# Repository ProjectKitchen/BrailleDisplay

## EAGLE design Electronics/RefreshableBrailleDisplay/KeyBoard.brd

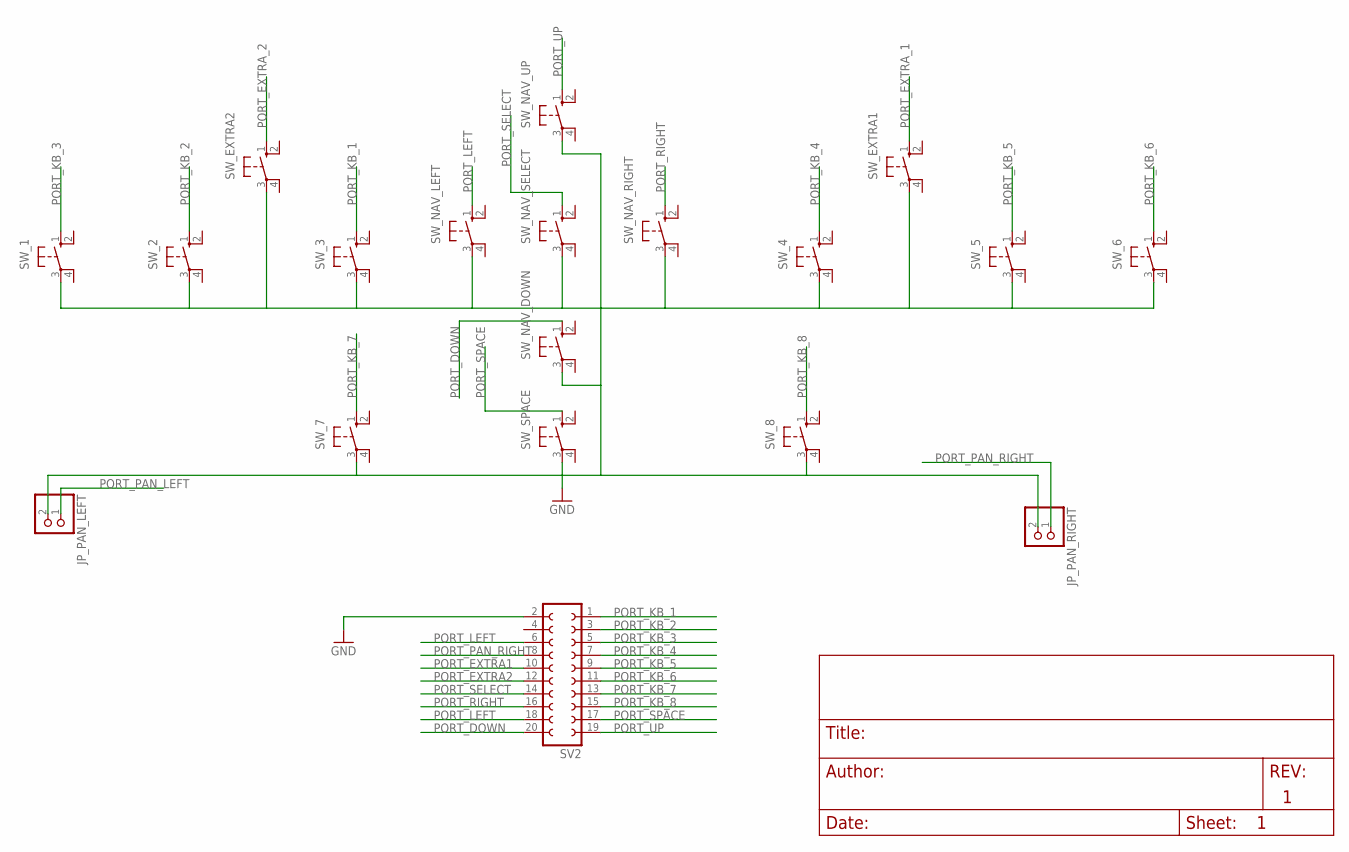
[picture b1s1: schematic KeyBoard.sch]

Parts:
JP_PAN_LEFT: PINHD-1X2; 1X02
JP_PAN_RIGHT: PINHD-1X2; 1X02
SV2: FE10-2
SW_1, SW_2, SW_3, SW_4, SW_5, SW_6, SW_7, SW_8: 10-XX; B3F-10XX
SW_EXTRA1, SW_EXTRA2: 10-XX; B3F-10XX
SW_NAV_DOWN: 10-XX; B3F-10XX
SW_NAV_LEFT: 10-XX; B3F-10XX
SW_NAV_RIGHT: 10-XX; B3F-10XX
SW_NAV_SELECT: 10-XX; B3F-10XX
SW_NAV_UP: 10-XX; B3F-10XX
SW_SPACE: 10-XX; B3F-10XX

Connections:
GND: JP_PAN_LEFT.2, JP_PAN_RIGHT.2, SV2.2, SW_1.3, SW_2.3, SW_3.3, SW_4.3, SW_5.3, SW_6.3, SW_7.3, SW_8.3, SW_EXTRA1.3, SW_EXTRA2.3, SW_NAV_DOWN.3, SW_NAV_LEFT.3, SW_NAV_RIGHT.3, SW_NAV_SELECT.3, SW_NAV_UP.3, SW_SPACE.3
PORT_DOWN: SV2.20, SW_NAV_DOWN.1 (S)
PORT_EXTRA1: SV2.10
PORT_EXTRA2: SV2.12
PORT_EXTRA_1: SW_EXTRA1.1 (S)
PORT_EXTRA_2: SW_EXTRA2.1 (S)
PORT_KB_1: SV2.1, SW_3.1 (S)
PORT_KB_2: SV2.3, SW_2.1 (S)
PORT_KB_3: SV2.5, SW_1.1 (S)
PORT_KB_4: SV2.7, SW_4.1 (S)
PORT_KB_5: SV2.9, SW_5.1 (S)
PORT_KB_6: SV2.11, SW_6.1 (S)
PORT_KB_7: SV2.13, SW_7.1 (S)
PORT_KB_8: SV2.15, SW_8.1 (S)
PORT_LEFT: SV2.6, SV2.18, SW_NAV_LEFT.1 (S)
PORT_PAN_LEFT: JP_PAN_LEFT.1
PORT_PAN_RIGHT: JP_PAN_RIGHT.1, SV2.8
PORT_RIGHT: SV2.16, SW_NAV_RIGHT.1 (S)
PORT_SELECT: SV2.14, SW_NAV_SELECT.1 (S)
PORT_SPACE: SV2.17, SW_SPACE.1 (S)
PORT_UP: SV2.19, SW_NAV_UP.1 (S)

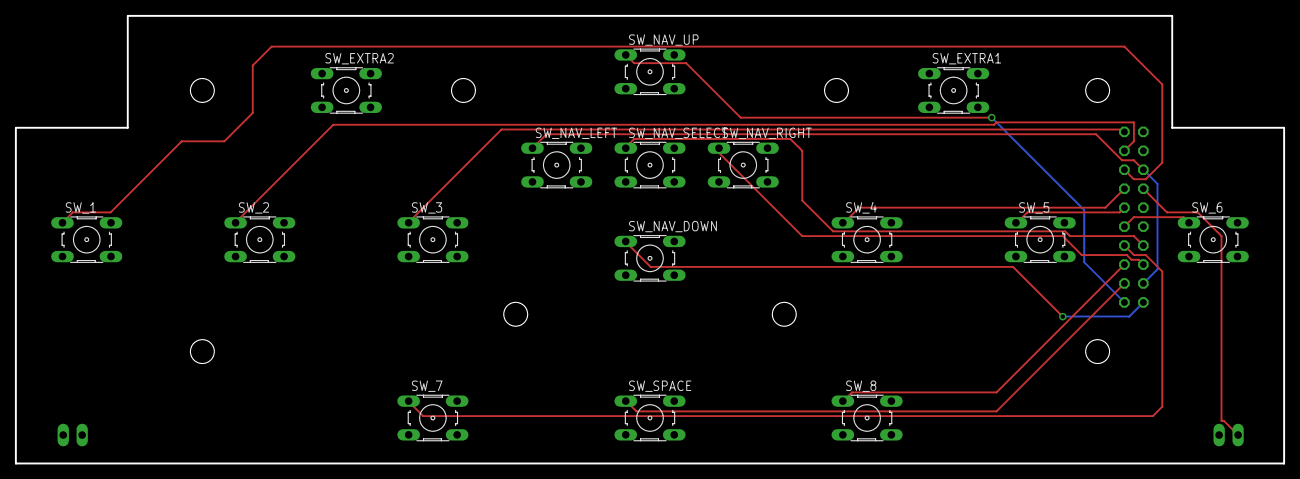
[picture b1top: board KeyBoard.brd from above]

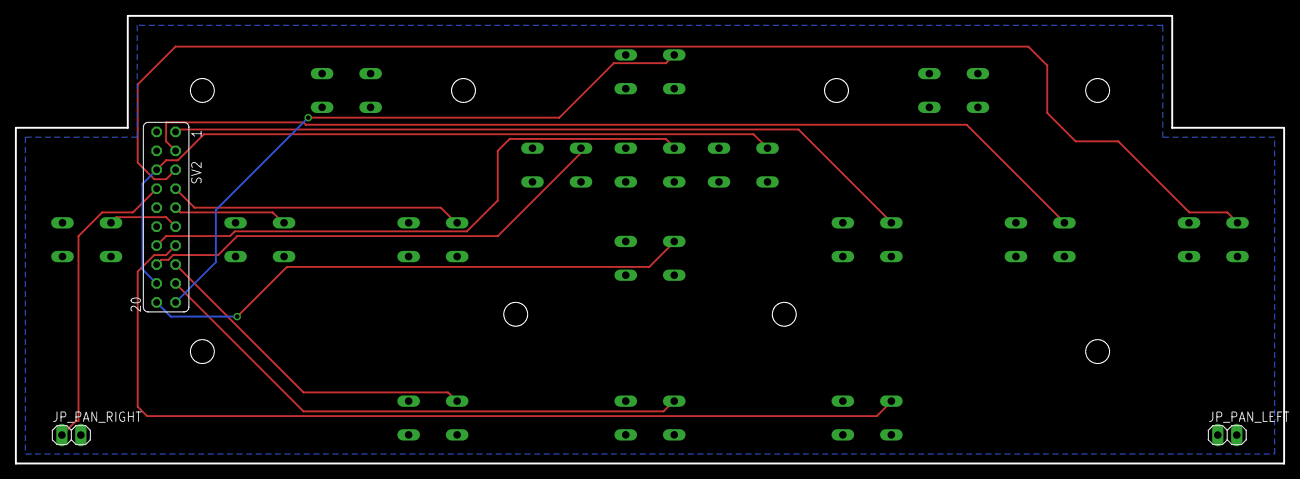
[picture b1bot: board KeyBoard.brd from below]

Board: 2 copper layers, 170.0 x 60.0 mm, 19 parts (3 on the bottom side), 16 nets.

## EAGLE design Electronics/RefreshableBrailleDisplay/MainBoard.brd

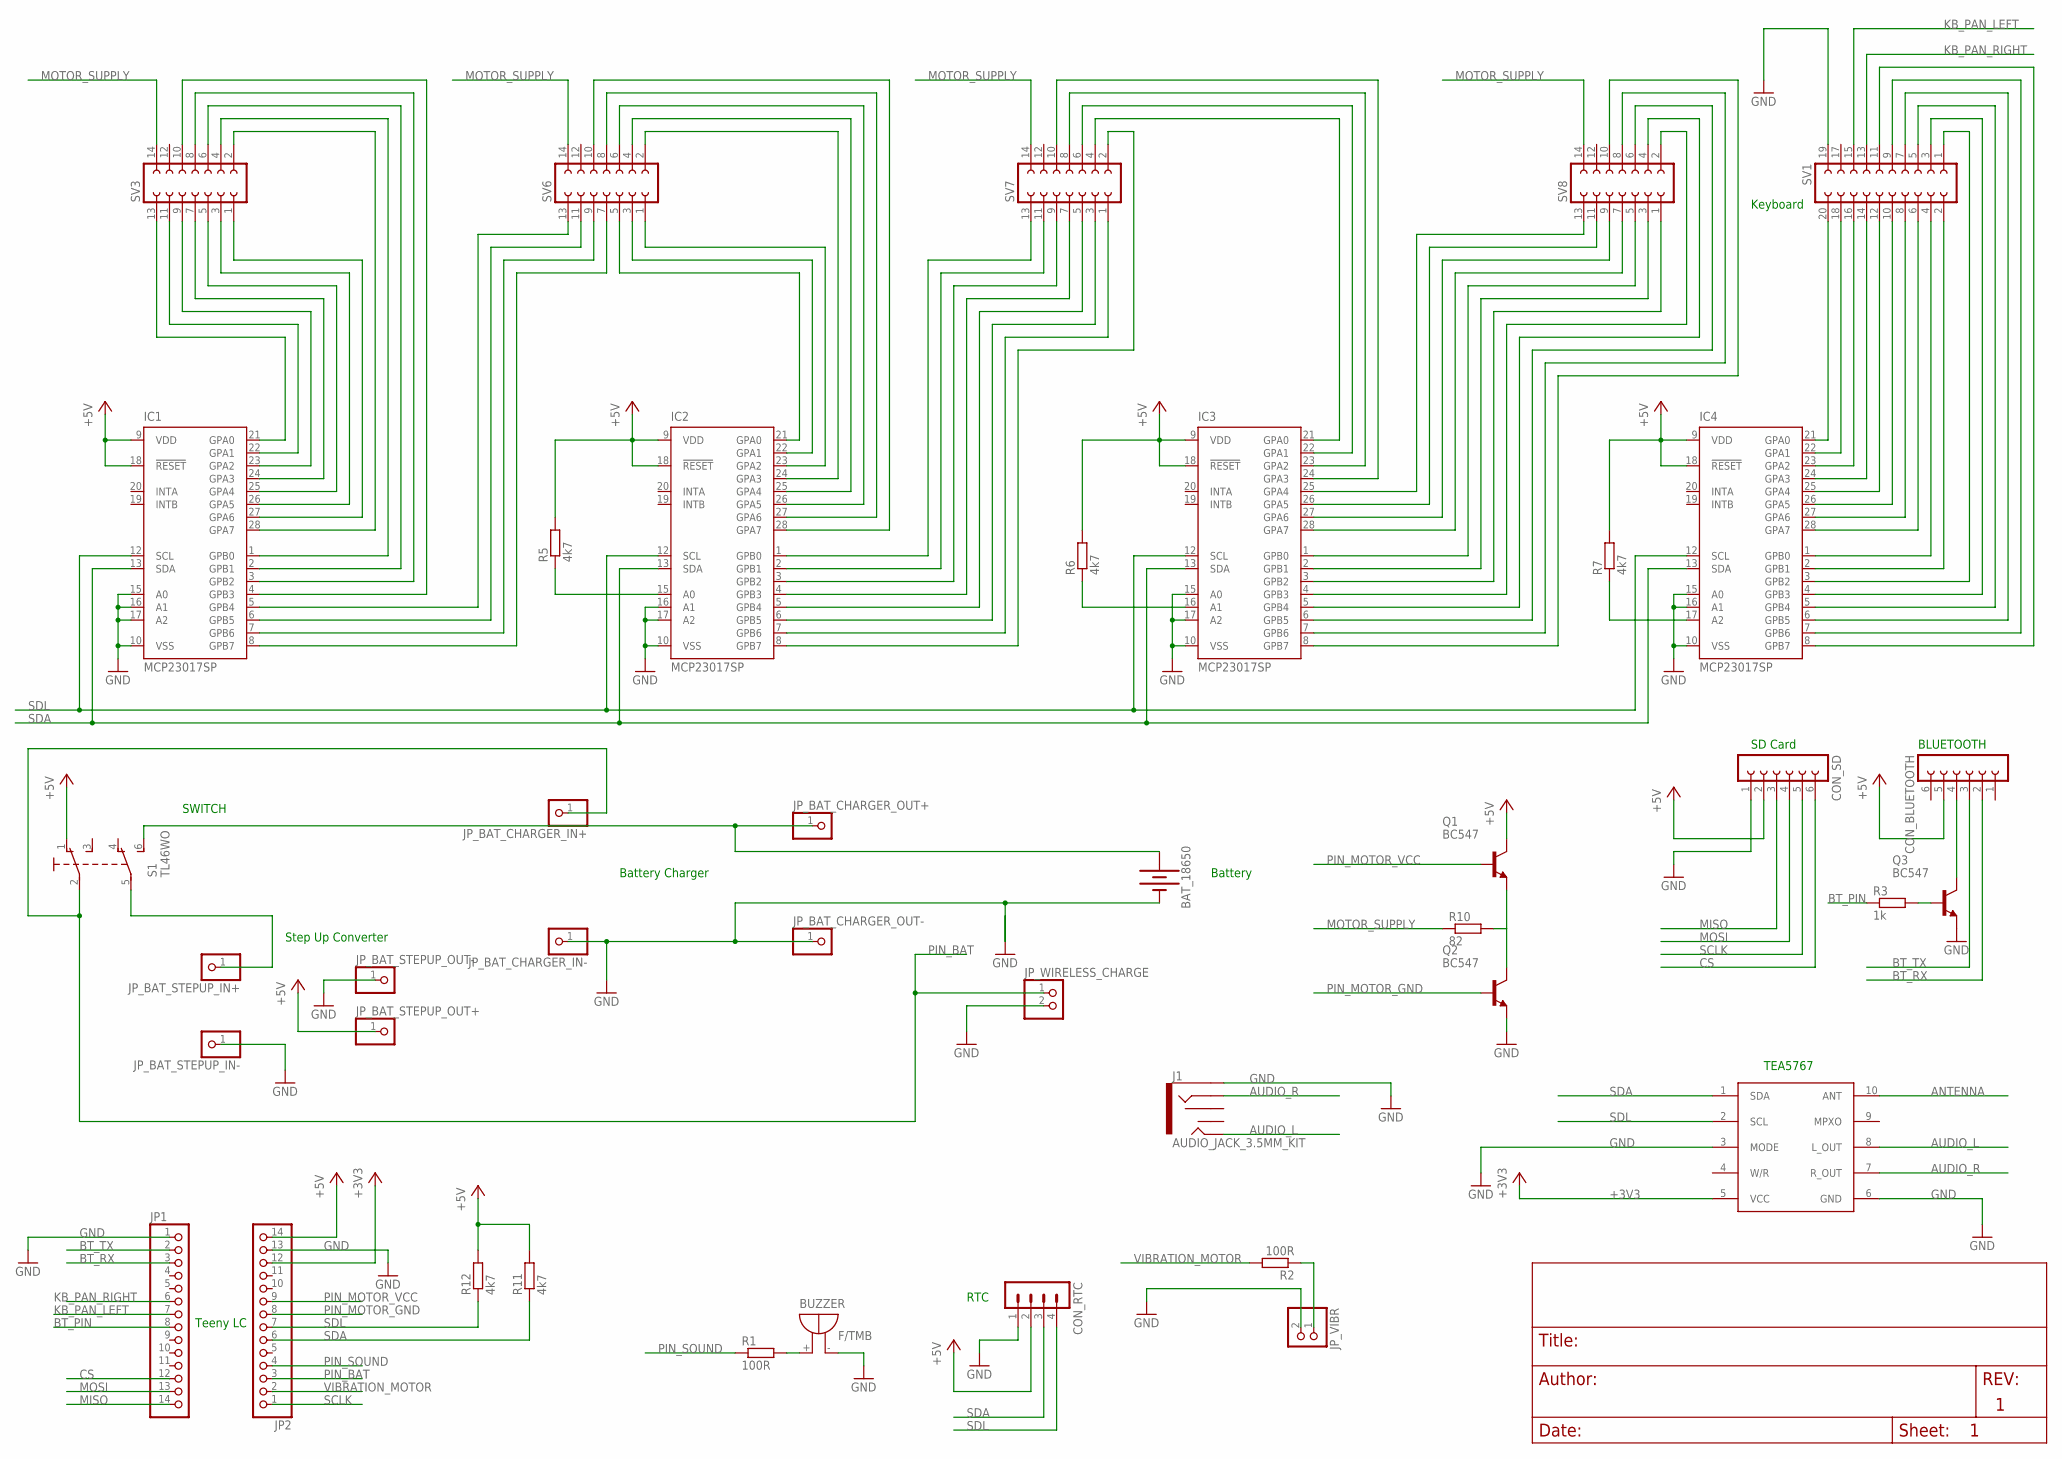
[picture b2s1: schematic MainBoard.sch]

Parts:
BAT_18650: BATTERY-18650; BATTERY_18650-HOLDER
BUZZER: F/TMB
CON_BLUETOOTH: FE06-1; FE06
CON_RTC: MA04-1
CON_SD: FE06-1; FE06
IC1, IC2, IC3, IC4: MCP23017SP; DIL28-3
J1: AUDIO_JACK_3.5MM_KIT; AUDIO-JACK-KIT
JP1, JP2: PINHD-1X14; 1X14
JP_BAT_CHARGER_IN+: PINHD-1X1; 1X01
JP_BAT_CHARGER_IN-: PINHD-1X1; 1X01
JP_BAT_CHARGER_OUT+: PINHD-1X1; 1X01
JP_BAT_CHARGER_OUT-: PINHD-1X1; 1X01
JP_BAT_STEPUP_IN+: PINHD-1X1; 1X01
JP_BAT_STEPUP_IN-: PINHD-1X1; 1X01
JP_BAT_STEPUP_OUT+: PINHD-1X1; 1X01
JP_BAT_STEPUP_OUT-: PINHD-1X1; 1X01
JP_VIBR: PINHD-1X2; 1X02
JP_WIRELESS_CHARGE: PINHD-1X2; 1X02
Q1, Q2, Q3: BC547; TO92
R1, R2: 100R; R1206
R3: 1k; R1206
R5, R6, R7, R11, R12: 4k7; R1206
R10: 82; R1206
S1: TL46WO; TL4XWO
SV1: FE10-2
SV3, SV6, SV7, SV8: FE07-2
TEA5767: TEA5767BREAKOUT; TEA5767MM2

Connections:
+3V3: JP2.12, TEA5767.5 (VCC)
+5V: CON_BLUETOOTH.5, CON_RTC.2, CON_SD.2, IC1.9 (VDD), IC1.18 (!RESET), IC2.9 (VDD), IC2.18 (!RESET), IC3.9 (VDD), IC3.18 (!RESET), IC4.9 (VDD), IC4.18 (!RESET), JP2.14, JP_BAT_STEPUP_OUT+.1, Q1.3 (C), R5.2, R6.2, R7.2, R11.2, R12.2, S1.1 (O)
ANTENNA: TEA5767.10 (ANT)
AUDIO_L: J1.TIP, TEA5767.8 (L_OUT)
AUDIO_R: J1.RING, TEA5767.7 (R_OUT)
BAT_PLUS: BAT_18650.PWR@1 (+), JP_BAT_CHARGER_OUT+.1, S1.6 (S1)
BT_PIN: JP1.8, R3.1
BT_RX: CON_BLUETOOTH.2, JP1.3
BT_TX: CON_BLUETOOTH.3, JP1.2
CS: CON_SD.6, JP1.12
GND: BAT_18650.GND@1 (-), BUZZER.-, CON_RTC.1, CON_SD.1, IC1.10 (VSS), IC1.15 (A0), IC1.16 (A1), IC1.17 (A2), IC2.10 (VSS), IC2.16 (A1), IC2.17 (A2), IC3.10 (VSS), IC3.15 (A0), IC3.17 (A2), IC4.10 (VSS), IC4.15 (A0), IC4.16 (A1), J1.SLEEVE, JP1.1, JP2.13, JP_BAT_CHARGER_IN-.1, JP_BAT_CHARGER_OUT-.1, JP_BAT_STEPUP_IN-.1, JP_BAT_STEPUP_OUT-.1, JP_VIBR.2, JP_WIRELESS_CHARGE.2, Q2.1 (E), Q3.1 (E), SV1.19, TEA5767.3 (MODE), TEA5767.6 (GND)
KB_PAN_LEFT: JP1.7, SV1.15
KB_PAN_RIGHT: JP1.6, SV1.13
MISO: CON_SD.3, JP1.14
MOSI: CON_SD.4, JP1.13
MOTOR_SUPPLY: R10.1, SV3.14, SV6.14, SV7.14, SV8.14
unnamed: IC4.25 (GPA4), SV1.12
unnamed: Q1.1 (E), Q2.3 (C), R10.2
unnamed: IC1.5 (GPB4), SV6.13
unnamed: IC4.26 (GPA5), SV1.10
unnamed: IC4.27 (GPA6), SV1.8
unnamed: IC4.28 (GPA7), SV1.6
unnamed: IC4.1 (GPB0), SV1.4
unnamed: IC4.24 (GPA3), SV1.14
unnamed: IC4.23 (GPA2), SV1.16
unnamed: IC4.22 (GPA1), SV1.18
unnamed: IC4.21 (GPA0), SV1.20
unnamed: IC4.2 (GPB1), SV1.2
unnamed: IC4.3 (GPB2), SV1.1
unnamed: IC4.4 (GPB3), SV1.3
unnamed: IC4.5 (GPB4), SV1.5
unnamed: IC4.6 (GPB5), SV1.7
unnamed: IC4.7 (GPB6), SV1.9
unnamed: IC4.8 (GPB7), SV1.11
unnamed: IC1.6 (GPB5), SV6.11
unnamed: IC3.4 (GPB3), SV8.2
unnamed: CON_BLUETOOTH.4, Q3.3 (C)
unnamed: IC2.2 (GPB1), SV7.11
unnamed: Q3.2 (B), R3.2
unnamed: BUZZER.+, R1.2
unnamed: JP_VIBR.1, R2.1
unnamed: JP_BAT_STEPUP_IN+.1, S1.5 (P1)
unnamed: IC1.7 (GPB6), SV6.9
unnamed: IC1.8 (GPB7), SV6.7
unnamed: IC3.21 (GPA0), SV7.4
unnamed: IC2.22 (GPA1), SV6.3
unnamed: IC2.25 (GPA4), SV6.4
unnamed: IC2.26 (GPA5), SV6.6
unnamed: IC2.27 (GPA6), SV6.8
unnamed: IC2.28 (GPA7), SV6.10
unnamed: IC2.1 (GPB0), SV7.13
unnamed: IC2.3 (GPB2), SV7.9
unnamed: IC2.4 (GPB3), SV7.7
unnamed: IC2.5 (GPB4), SV7.5
unnamed: IC1.24 (GPA3), SV3.7
unnamed: IC1.23 (GPA2), SV3.9
unnamed: IC1.22 (GPA1), SV3.11
unnamed: IC1.25 (GPA4), SV3.5
unnamed: IC1.26 (GPA5), SV3.3
unnamed: IC1.27 (GPA6), SV3.1
unnamed: IC1.28 (GPA7), SV3.2
unnamed: IC1.1 (GPB0), SV3.4
unnamed: IC1.2 (GPB1), SV3.6
unnamed: IC1.3 (GPB2), SV3.8
unnamed: IC1.4 (GPB3), SV3.10
unnamed: IC4.17 (A2), R7.1
unnamed: IC3.16 (A1), R6.1
unnamed: IC2.15 (A0), R5.1
unnamed: IC3.22 (GPA1), SV7.6
unnamed: IC2.7 (GPB6), SV7.1
unnamed: IC1.21 (GPA0), SV3.13
unnamed: IC2.8 (GPB7), SV7.2
unnamed: IC2.6 (GPB5), SV7.3
unnamed: IC2.24 (GPA3), SV6.2
unnamed: IC2.21 (GPA0), SV6.5
unnamed: IC2.23 (GPA2), SV6.1
unnamed: IC3.23 (GPA2), SV7.8
unnamed: IC3.26 (GPA5), SV8.11
unnamed: IC3.6 (GPB5), SV8.6
unnamed: IC3.8 (GPB7), SV8.10
unnamed: IC3.7 (GPB6), SV8.8
unnamed: IC3.5 (GPB4), SV8.4
unnamed: IC3.3 (GPB2), SV8.1
unnamed: IC3.2 (GPB1), SV8.3
unnamed: IC3.1 (GPB0), SV8.5
unnamed: IC3.28 (GPA7), SV8.7
unnamed: IC3.27 (GPA6), SV8.9
unnamed: IC3.25 (GPA4), SV8.13
unnamed: IC3.24 (GPA3), SV7.10
PIN_BAT: JP2.3, JP_BAT_CHARGER_IN+.1, JP_WIRELESS_CHARGE.1, S1.2
PIN_MOTOR_GND: JP2.8, Q2.2 (B)
PIN_MOTOR_VCC: JP2.9, Q1.2 (B)
PIN_SOUND: JP2.4, R1.1
SCLK: CON_SD.5, JP2.1
SDA: CON_RTC.3, IC1.13 (SDA), IC2.13 (SDA), IC3.13 (SDA), IC4.13 (SDA), JP2.6, R11.1, TEA5767.1 (SDA)
SDL: CON_RTC.4, IC1.12 (SCL), IC2.12 (SCL), IC3.12 (SCL), IC4.12 (SCL), JP2.7, R12.1, TEA5767.2 (SCL)
VIBRATION_MOTOR: JP2.2, R2.2

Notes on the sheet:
Keyboard
Battery
RTC
SD Card
SWITCH
BLUETOOTH
Step Up Converter
Battery Charger
Teeny LC
TEA5767

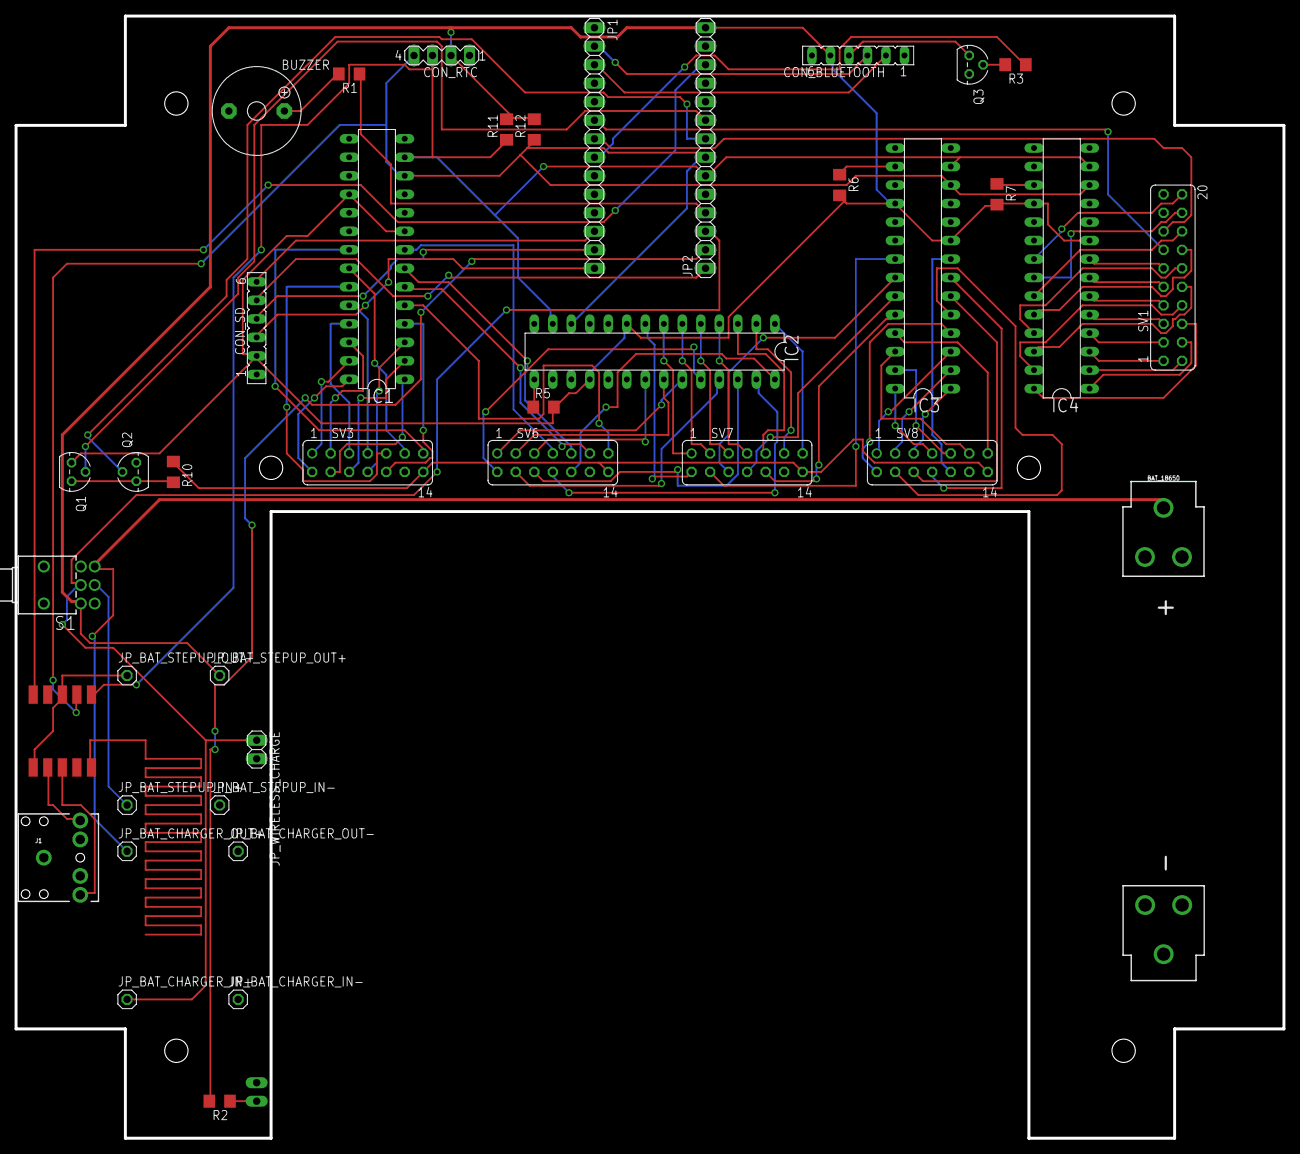
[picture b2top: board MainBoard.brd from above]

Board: 2 copper layers, 174.0 x 154.0 mm, 41 parts (1 on the bottom side), 96 nets.

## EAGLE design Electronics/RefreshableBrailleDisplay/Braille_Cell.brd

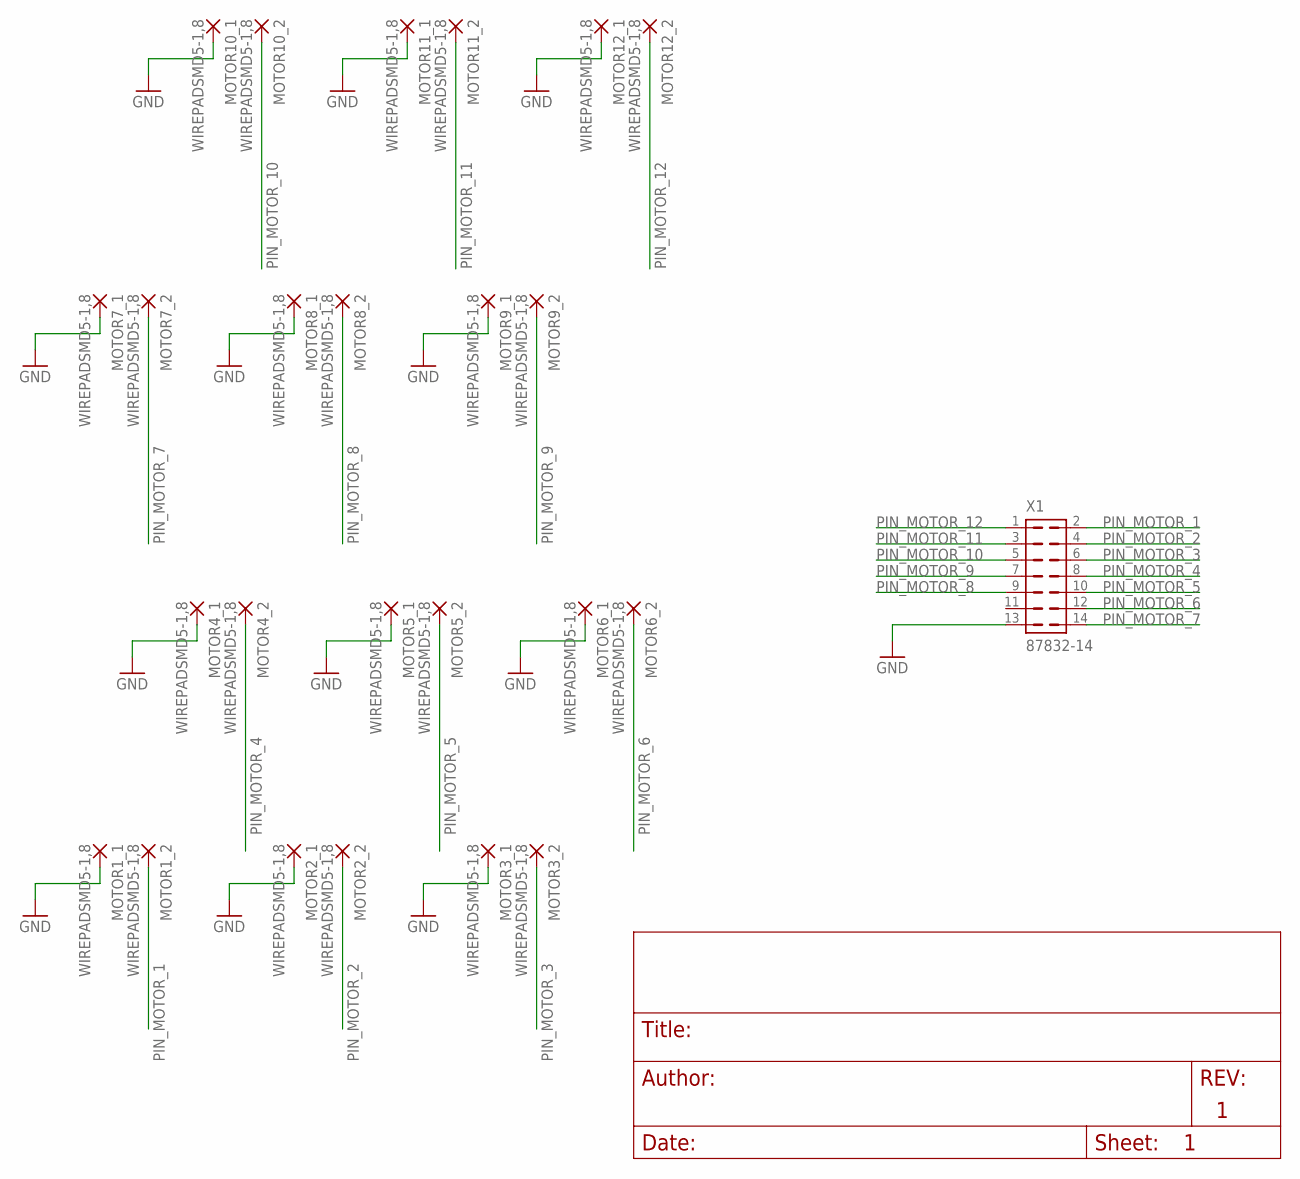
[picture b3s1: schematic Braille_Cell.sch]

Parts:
MOTOR1_1, MOTOR1_2, MOTOR2_1, MOTOR2_2, MOTOR3_1, MOTOR3_2, MOTOR4_1, MOTOR4_2, MOTOR5_1, MOTOR5_2, MOTOR6_1, MOTOR6_2, MOTOR7_1, MOTOR7_2, MOTOR8_1, MOTOR8_2, MOTOR9_1, MOTOR9_2, MOTOR10_1, MOTOR10_2, MOTOR11_1, MOTOR11_2, MOTOR12_1, MOTOR12_2: WIREPADSMD5-1,8; 5-1,8
X1: 87832-14

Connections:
GND: MOTOR1_1.1, MOTOR2_1.1, MOTOR3_1.1, MOTOR4_1.1, MOTOR5_1.1, MOTOR6_1.1, MOTOR7_1.1, MOTOR8_1.1, MOTOR9_1.1, MOTOR10_1.1, MOTOR11_1.1, MOTOR12_1.1, X1.13
PIN_MOTOR_1: MOTOR1_2.1, X1.2
PIN_MOTOR_2: MOTOR2_2.1, X1.4
PIN_MOTOR_3: MOTOR3_2.1, X1.6
PIN_MOTOR_4: MOTOR4_2.1, X1.8
PIN_MOTOR_5: MOTOR5_2.1, X1.10
PIN_MOTOR_6: MOTOR6_2.1, X1.12
PIN_MOTOR_7: MOTOR7_2.1, X1.14
PIN_MOTOR_8: MOTOR8_2.1, X1.9
PIN_MOTOR_9: MOTOR9_2.1, X1.7
PIN_MOTOR_10: MOTOR10_2.1, X1.5
PIN_MOTOR_11: MOTOR11_2.1, X1.3
PIN_MOTOR_12: MOTOR12_2.1, X1.1

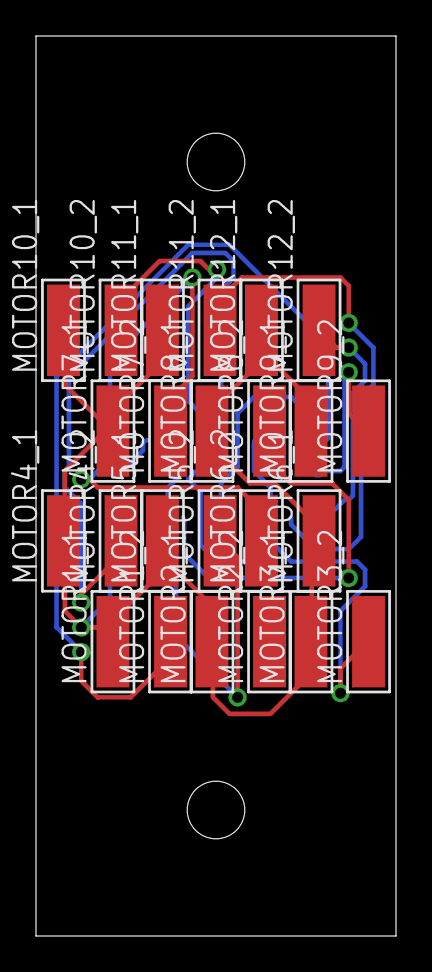
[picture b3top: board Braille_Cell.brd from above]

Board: 2 copper layers, 20.0 x 50.0 mm, 25 parts (1 on the bottom side), 13 nets.

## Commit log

2017-05-22 BrailleDisplay
    Designed and developed by Christoph Ulbinger
2017-05-22 License
2017-09-14 added documentation

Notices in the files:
parts and their libraries:
SparkFun-Batteries: Licensing: Creative Commons ShareAlike 4.0 International - https://creativecommons.org/licenses/by-sa/4.0
